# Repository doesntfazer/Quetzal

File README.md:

# Quetzal

100% ergo keyboard based on rp2040 Zero Board

Keyboard is tested and working.

Firmware for this board will be in the [Keyboard Dweebs Firmware Repository](https://github.com/doesntfazer/Keyboard-Dweebs-Firmware-repository)

This Board will be using [PRK Firmware](https://github.com/picoruby/prk_firmware) because of the support for Japanese duplex Matrices.

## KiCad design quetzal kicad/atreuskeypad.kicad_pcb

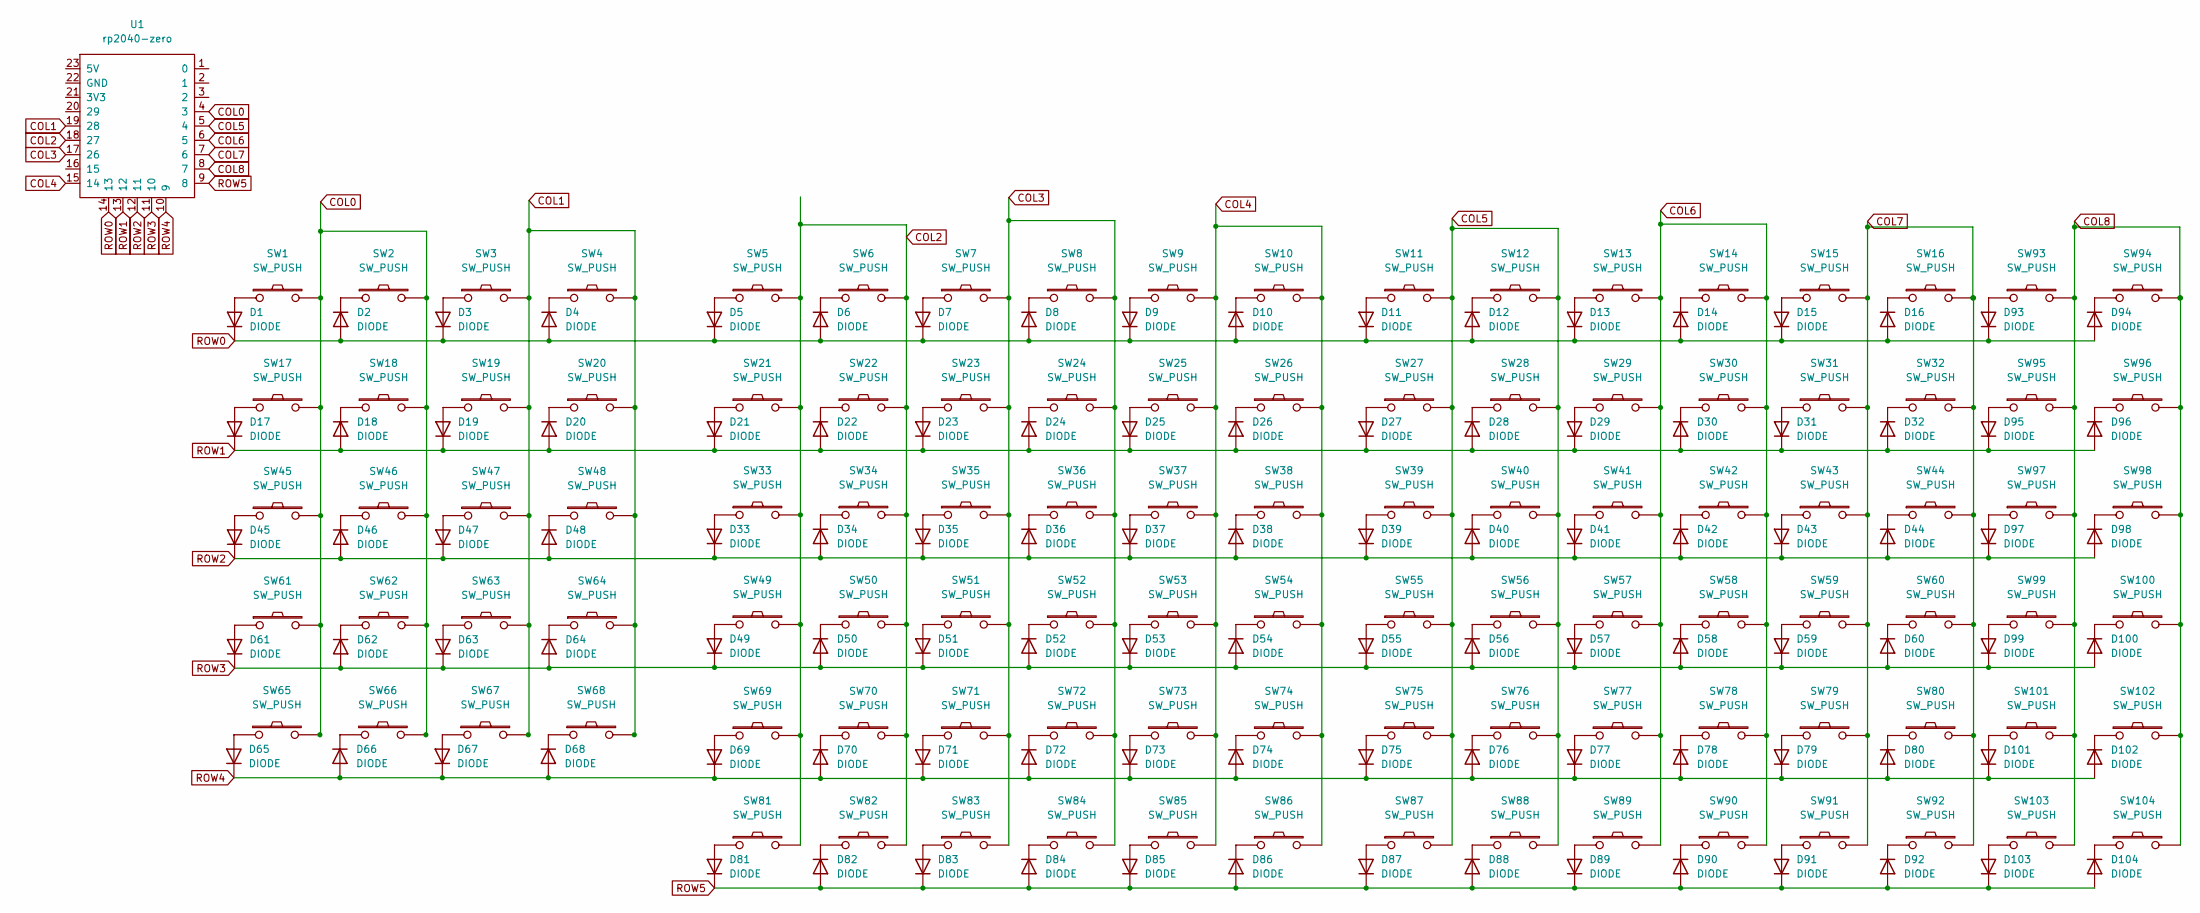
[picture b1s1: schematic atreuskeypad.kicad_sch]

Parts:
D1, D2, D3, D4, D5, D6, D7, D8, D9, D10, D11, D12, D13, D14, D15, D16, D17, D18, D19, D20, D21, D22, D23, D24, D25, D26, D27, D28, D29, D30, D31, D32, D33, D34, D35, D36, D37, D38, D39, D40, D41, D42, D43, D44, D45, D46, D47, D48, D49, D50, D51, D52, D53, D54, D55, D56, D57, D58, D59, D60, D61, D62, D63, D64, D65, D66, D67, D68, D69, D70, D71, D72, D73, D74, D75, D76, D77, D78, D79, D80, D81, D82, D83, D84, D85, D86, D87, D88, D89, D90, D91, D92, D93, D94, D95, D96, D97, D98, D99, D100, D101, D102, D103, D104: DIODE; D_SOD-123
SW1, SW2, SW3, SW4, SW5, SW6, SW7, SW8, SW9, SW10, SW11, SW12, SW13, SW14, SW15, SW16, SW17, SW18, SW19, SW20, SW21, SW22, SW23, SW24, SW25, SW26, SW27, SW28, SW29, SW30, SW31, SW32, SW33, SW34, SW35, SW36, SW37, SW38, SW39, SW40, SW41, SW42, SW43, SW44, SW45, SW46, SW47, SW48, SW49, SW50, SW51, SW52, SW53, SW54, SW55, SW56, SW57, SW58, SW59, SW60, SW61, SW62, SW63, SW64, SW65, SW66, SW67, SW68, SW69, SW70, SW71, SW72, SW73, SW74, SW75, SW76, SW77, SW78, SW79, SW80, SW81, SW82, SW83, SW84, SW85, SW86, SW87, SW88, SW89, SW90, SW91, SW92, SW93, SW94, SW95, SW96, SW97, SW98, SW99, SW100, SW101, SW102, SW103, SW104: SW_PUSH
U1: rp2040-zero; rp2040-zero-smd-no-cut

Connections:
COL0: SW1.2, SW2.2, SW17.2, SW18.2, SW45.2, SW46.2, SW61.2, SW62.2, SW65.2, SW66.2, U1.4 (3)
COL1: SW3.2, SW4.2, SW19.2, SW20.2, SW47.2, SW48.2, SW63.2, SW64.2, SW67.2, SW68.2, U1.19 (28)
COL2: SW5.2, SW6.2, SW21.2, SW22.2, SW33.2, SW34.2, SW49.2, SW50.2, SW69.2, SW70.2, SW81.2, SW82.2, U1.18 (27)
COL3: SW7.2, SW8.2, SW23.2, SW24.2, SW35.2, SW36.2, SW51.2, SW52.2, SW71.2, SW72.2, SW83.2, SW84.2, U1.17 (26)
COL4: SW9.2, SW10.2, SW25.2, SW26.2, SW37.2, SW38.2, SW53.2, SW54.2, SW73.2, SW74.2, SW85.2, SW86.2, U1.15 (14)
COL5: SW11.2, SW12.2, SW27.2, SW28.2, SW39.2, SW40.2, SW55.2, SW56.2, SW75.2, SW76.2, SW87.2, SW88.2, U1.5 (4)
COL6: SW13.2, SW14.2, SW29.2, SW30.2, SW41.2, SW42.2, SW57.2, SW58.2, SW77.2, SW78.2, SW89.2, SW90.2, U1.6 (5)
COL7: SW15.2, SW16.2, SW31.2, SW32.2, SW43.2, SW44.2, SW59.2, SW60.2, SW79.2, SW80.2, SW91.2, SW92.2, U1.7 (6)
COL8: SW93.2, SW94.2, SW95.2, SW96.2, SW97.2, SW98.2, SW99.2, SW100.2, SW101.2, SW102.2, SW103.2, SW104.2, U1.8 (7)
unnamed: D1.1 (A), SW1.1
unnamed: D2.2 (K), SW2.1
unnamed: D3.1 (A), SW3.1
unnamed: D4.2 (K), SW4.1
unnamed: D5.1 (A), SW5.1
unnamed: D6.2 (K), SW6.1
unnamed: D7.1 (A), SW7.1
unnamed: D8.2 (K), SW8.1
unnamed: D9.1 (A), SW9.1
unnamed: D10.2 (K), SW10.1
unnamed: D11.1 (A), SW11.1
unnamed: D12.2 (K), SW12.1
unnamed: D13.1 (A), SW13.1
unnamed: D14.2 (K), SW14.1
unnamed: D15.1 (A), SW15.1
unnamed: D16.2 (K), SW16.1
unnamed: D17.1 (A), SW17.1
unnamed: D18.2 (K), SW18.1
unnamed: D19.1 (A), SW19.1
unnamed: D20.2 (K), SW20.1
unnamed: D21.1 (A), SW21.1
unnamed: D22.2 (K), SW22.1
unnamed: D23.1 (A), SW23.1
unnamed: D24.2 (K), SW24.1
unnamed: D25.1 (A), SW25.1
unnamed: D26.2 (K), SW26.1
unnamed: D27.1 (A), SW27.1
unnamed: D28.2 (K), SW28.1
unnamed: D29.1 (A), SW29.1
unnamed: D30.2 (K), SW30.1
unnamed: D31.1 (A), SW31.1
unnamed: D32.2 (K), SW32.1
unnamed: D33.1 (A), SW33.1
unnamed: D34.2 (K), SW34.1
unnamed: D35.1 (A), SW35.1
unnamed: D36.2 (K), SW36.1
unnamed: D37.1 (A), SW37.1
unnamed: D38.2 (K), SW38.1
unnamed: D39.1 (A), SW39.1
unnamed: D40.2 (K), SW40.1
unnamed: D41.1 (A), SW41.1
unnamed: D42.2 (K), SW42.1
unnamed: D43.1 (A), SW43.1
unnamed: D44.2 (K), SW44.1
unnamed: D45.1 (A), SW45.1
unnamed: D46.2 (K), SW46.1
unnamed: D47.1 (A), SW47.1
unnamed: D48.2 (K), SW48.1
unnamed: D49.1 (A), SW49.1
unnamed: D50.2 (K), SW50.1
unnamed: D51.1 (A), SW51.1
unnamed: D52.2 (K), SW52.1
unnamed: D53.1 (A), SW53.1
unnamed: D54.2 (K), SW54.1
unnamed: D55.1 (A), SW55.1
unnamed: D56.2 (K), SW56.1
unnamed: D57.1 (A), SW57.1
unnamed: D58.2 (K), SW58.1
unnamed: D59.1 (A), SW59.1
unnamed: D60.2 (K), SW60.1
unnamed: D61.1 (A), SW61.1
unnamed: D62.2 (K), SW62.1
unnamed: D63.1 (A), SW63.1
unnamed: D64.2 (K), SW64.1
unnamed: D65.1 (A), SW65.1
unnamed: D66.2 (K), SW66.1
unnamed: D67.1 (A), SW67.1
unnamed: D68.2 (K), SW68.1
unnamed: D69.1 (A), SW69.1
unnamed: D70.2 (K), SW70.1
unnamed: D71.1 (A), SW71.1
unnamed: D72.2 (K), SW72.1
unnamed: D73.1 (A), SW73.1
unnamed: D74.2 (K), SW74.1
unnamed: D75.1 (A), SW75.1
unnamed: D76.2 (K), SW76.1
unnamed: D77.1 (A), SW77.1
unnamed: D78.2 (K), SW78.1
unnamed: D79.1 (A), SW79.1
unnamed: D80.2 (K), SW80.1
unnamed: D81.1 (A), SW81.1
unnamed: D82.2 (K), SW82.1
unnamed: D83.1 (A), SW83.1
unnamed: D84.2 (K), SW84.1
unnamed: D85.1 (A), SW85.1
unnamed: D86.2 (K), SW86.1
unnamed: D87.1 (A), SW87.1
unnamed: D88.2 (K), SW88.1
unnamed: D89.1 (A), SW89.1
unnamed: D90.2 (K), SW90.1
unnamed: D91.1 (A), SW91.1
unnamed: D92.2 (K), SW92.1
unnamed: D93.1 (A), SW93.1
unnamed: D94.2 (K), SW94.1
unnamed: D95.1 (A), SW95.1
unnamed: D96.2 (K), SW96.1
unnamed: D97.1 (A), SW97.1
unnamed: D98.2 (K), SW98.1
unnamed: D99.1 (A), SW99.1
unnamed: D100.2 (K), SW100.1
unnamed: D101.1 (A), SW101.1
unnamed: D102.2 (K), SW102.1
unnamed: D103.1 (A), SW103.1
unnamed: D104.2 (K), SW104.1
ROW0: D1.2 (K), D2.1 (A), D3.2 (K), D4.1 (A), D5.2 (K), D6.1 (A), D7.2 (K), D8.1 (A), D9.2 (K), D10.1 (A), D11.2 (K), D12.1 (A), D13.2 (K), D14.1 (A), D15.2 (K), D16.1 (A), D93.2 (K), D94.1 (A), U1.14 (13)
ROW1: D17.2 (K), D18.1 (A), D19.2 (K), D20.1 (A), D21.2 (K), D22.1 (A), D23.2 (K), D24.1 (A), D25.2 (K), D26.1 (A), D27.2 (K), D28.1 (A), D29.2 (K), D30.1 (A), D31.2 (K), D32.1 (A), D95.2 (K), D96.1 (A), U1.13 (12)
ROW2: D33.2 (K), D34.1 (A), D35.2 (K), D36.1 (A), D37.2 (K), D38.1 (A), D39.2 (K), D40.1 (A), D41.2 (K), D42.1 (A), D43.2 (K), D44.1 (A), D45.2 (K), D46.1 (A), D47.2 (K), D48.1 (A), D97.2 (K), D98.1 (A), U1.12 (11)
ROW3: D49.2 (K), D50.1 (A), D51.2 (K), D52.1 (A), D53.2 (K), D54.1 (A), D55.2 (K), D56.1 (A), D57.2 (K), D58.1 (A), D59.2 (K), D60.1 (A), D61.2 (K), D62.1 (A), D63.2 (K), D64.1 (A), D99.2 (K), D100.1 (A), U1.11 (10)
ROW4: D65.2 (K), D66.1 (A), D67.2 (K), D68.1 (A), D69.2 (K), D70.1 (A), D71.2 (K), D72.1 (A), D73.2 (K), D74.1 (A), D75.2 (K), D76.1 (A), D77.2 (K), D78.1 (A), D79.2 (K), D80.1 (A), D101.2 (K), D102.1 (A), U1.10 (9)
ROW5: D81.2 (K), D82.1 (A), D83.2 (K), D84.1 (A), D85.2 (K), D86.1 (A), D87.2 (K), D88.1 (A), D89.2 (K), D90.1 (A), D91.2 (K), D92.1 (A), D103.2 (K), D104.1 (A), U1.9 (8)

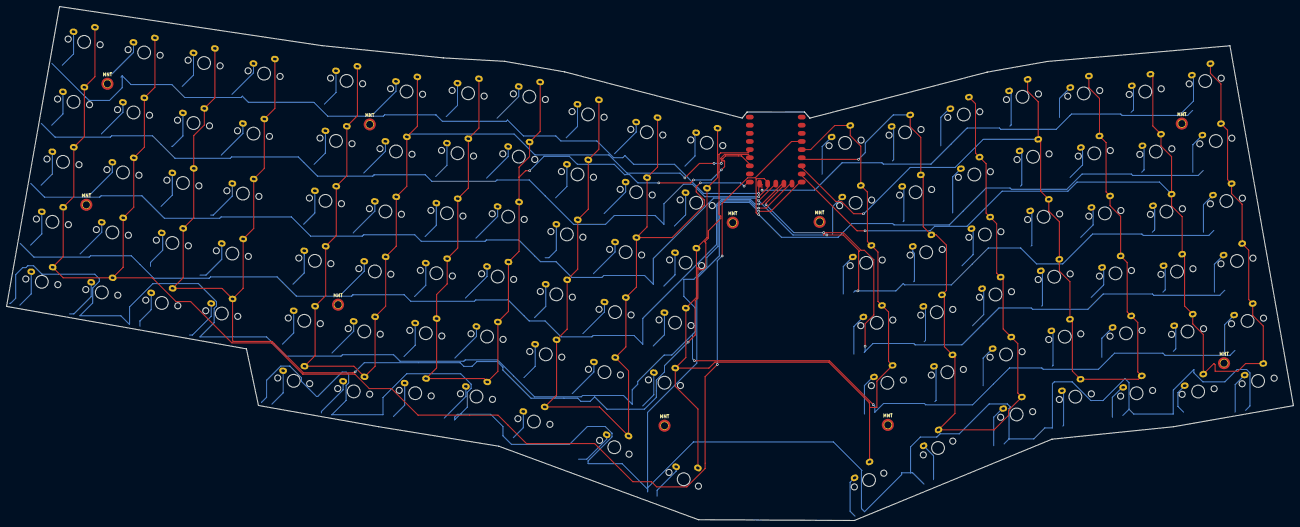
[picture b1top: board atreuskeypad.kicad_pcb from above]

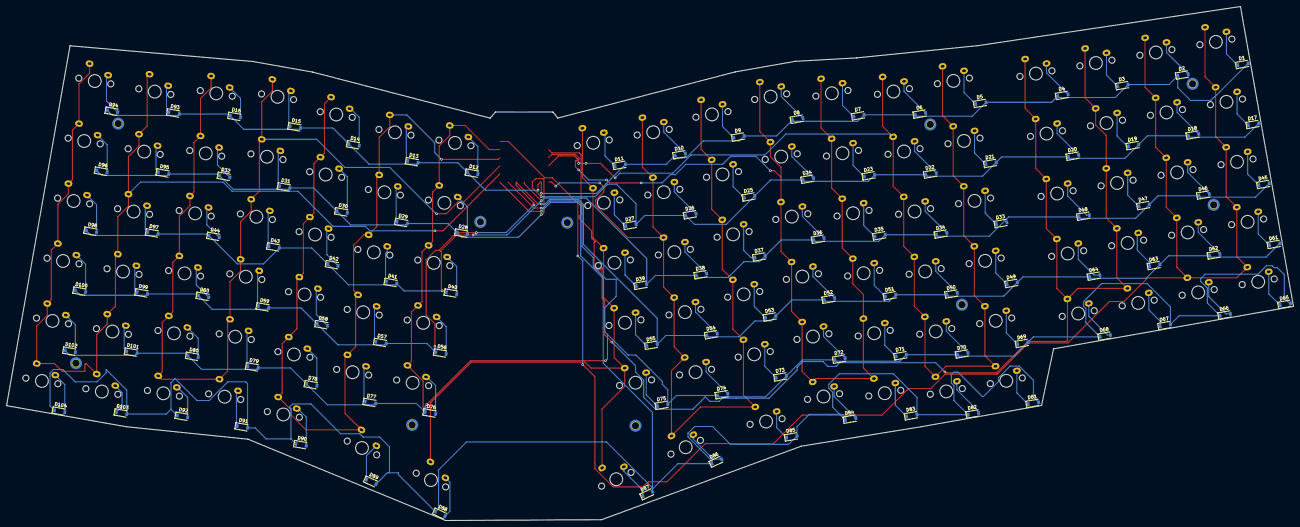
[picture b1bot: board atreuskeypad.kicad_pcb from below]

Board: 2 copper layers, 402.5 x 160.8 mm, 219 parts (104 on the bottom side), 119 nets.

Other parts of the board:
MNT: MountingHole_2.2mm_M2_DIN965_Pad_TopBottom
MNT#2, MNT#3, MNT#4, MNT#5, MNT#6, MNT#7, MNT#8, MNT#9, MNT#10: MountingHole_2.2mm_M2_DIN965_Pad_TopBottom

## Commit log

2022-12-23 added case files
2022-12-23 adding mask
2022-12-23 remove backup files
2022-12-23 updated gerber, added silkscreen
2022-12-23 touchups
2022-12-29 Fixed my dumb mistake
    The rp2040 Zero is supposed to have a cutout. I removed the cutout because it was causing issues with my kicad Gerber's. I added an appropriate cut back to this so that the MCU can sit flush.
2022-12-29 new gerbers with my fixed mistake
2022-12-29 added back the copper fill
    Back at it again with the stupid mistakes
2022-12-29 Gerber's with the fill
2022-12-30 cases
    added more cases
2022-12-31 renamed to lowpro
    Low profile - this means that the case comes up to the switch plate. (or on this case, where the switch plate would be if it weren't pcb mount.) You can still see the tops of the switches still.
2022-12-31 renamed to minimal
    Minimal means that it uses as little material as possible. Just enough to cover the pcb, and still to be fairly rigid.
2023-04-03 fixed backwards diode in schematic
    spice_simulation diode symbols are backwards compared to their PCB footprint. Changed all spice_simulation diode symbols to 1N4148W symbols and verified PCB now matches.
2023-04-12 Fixed formatting in readme
